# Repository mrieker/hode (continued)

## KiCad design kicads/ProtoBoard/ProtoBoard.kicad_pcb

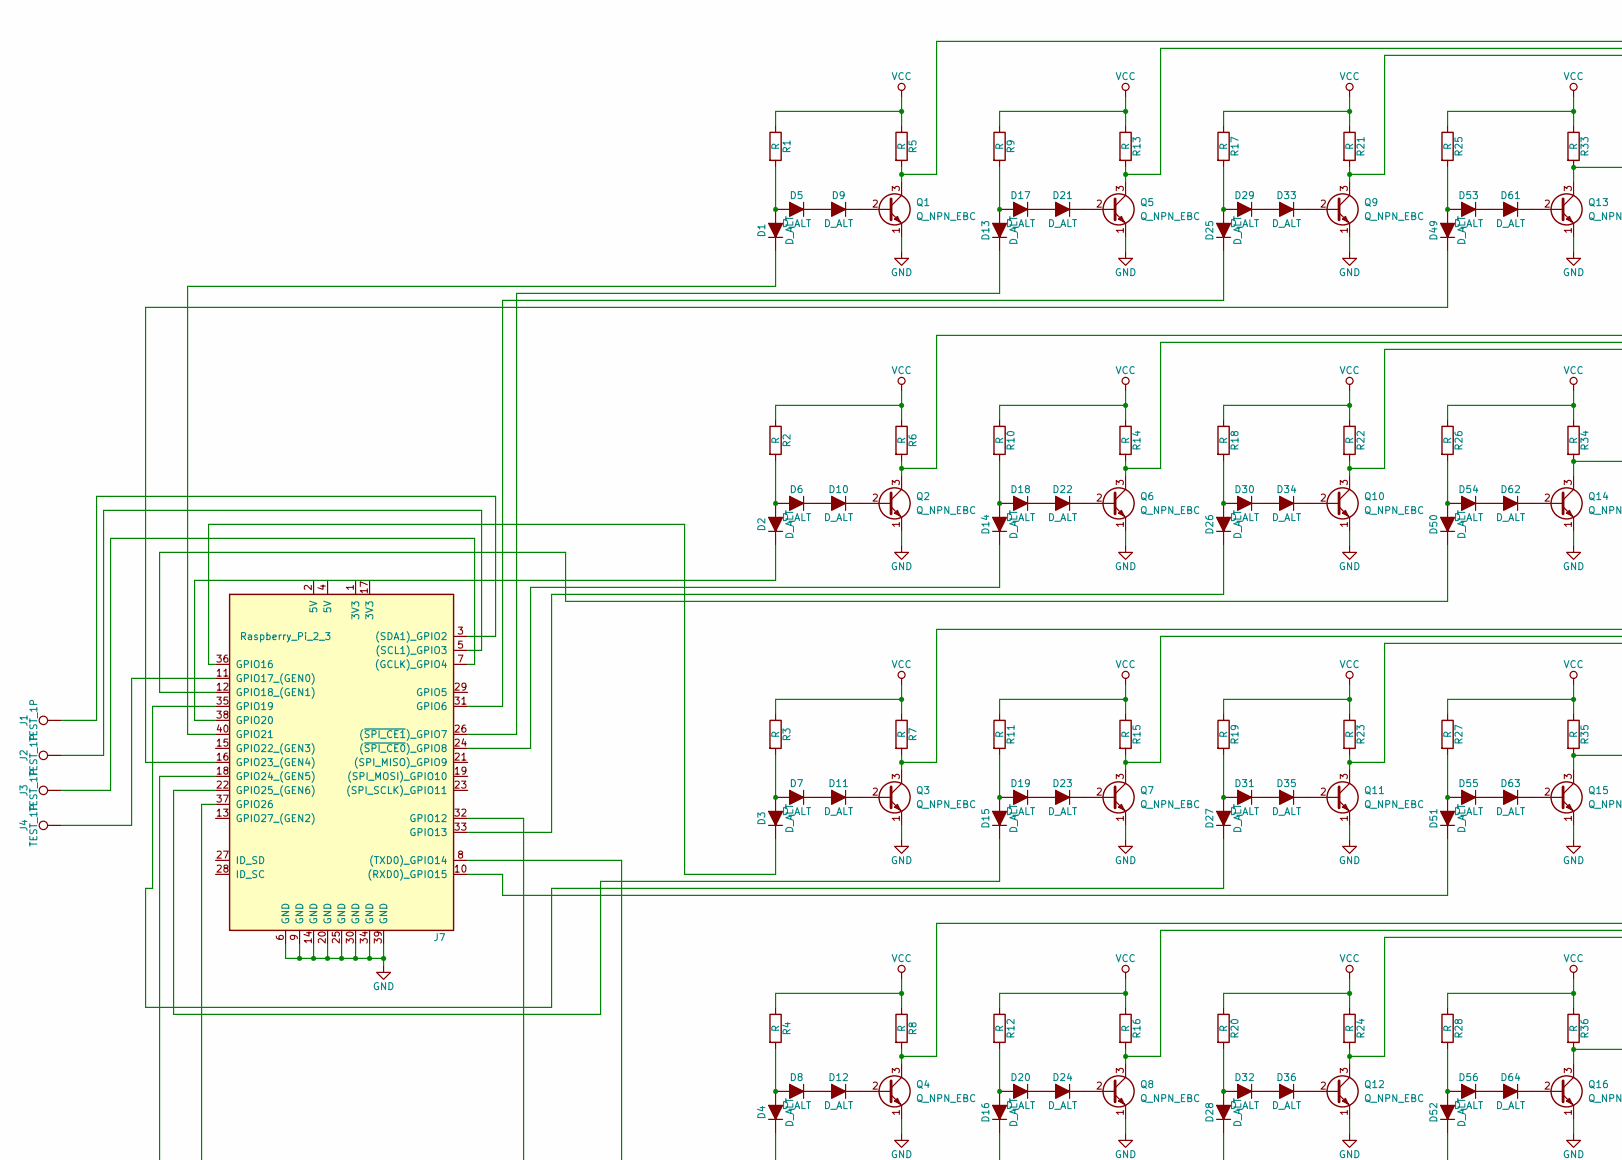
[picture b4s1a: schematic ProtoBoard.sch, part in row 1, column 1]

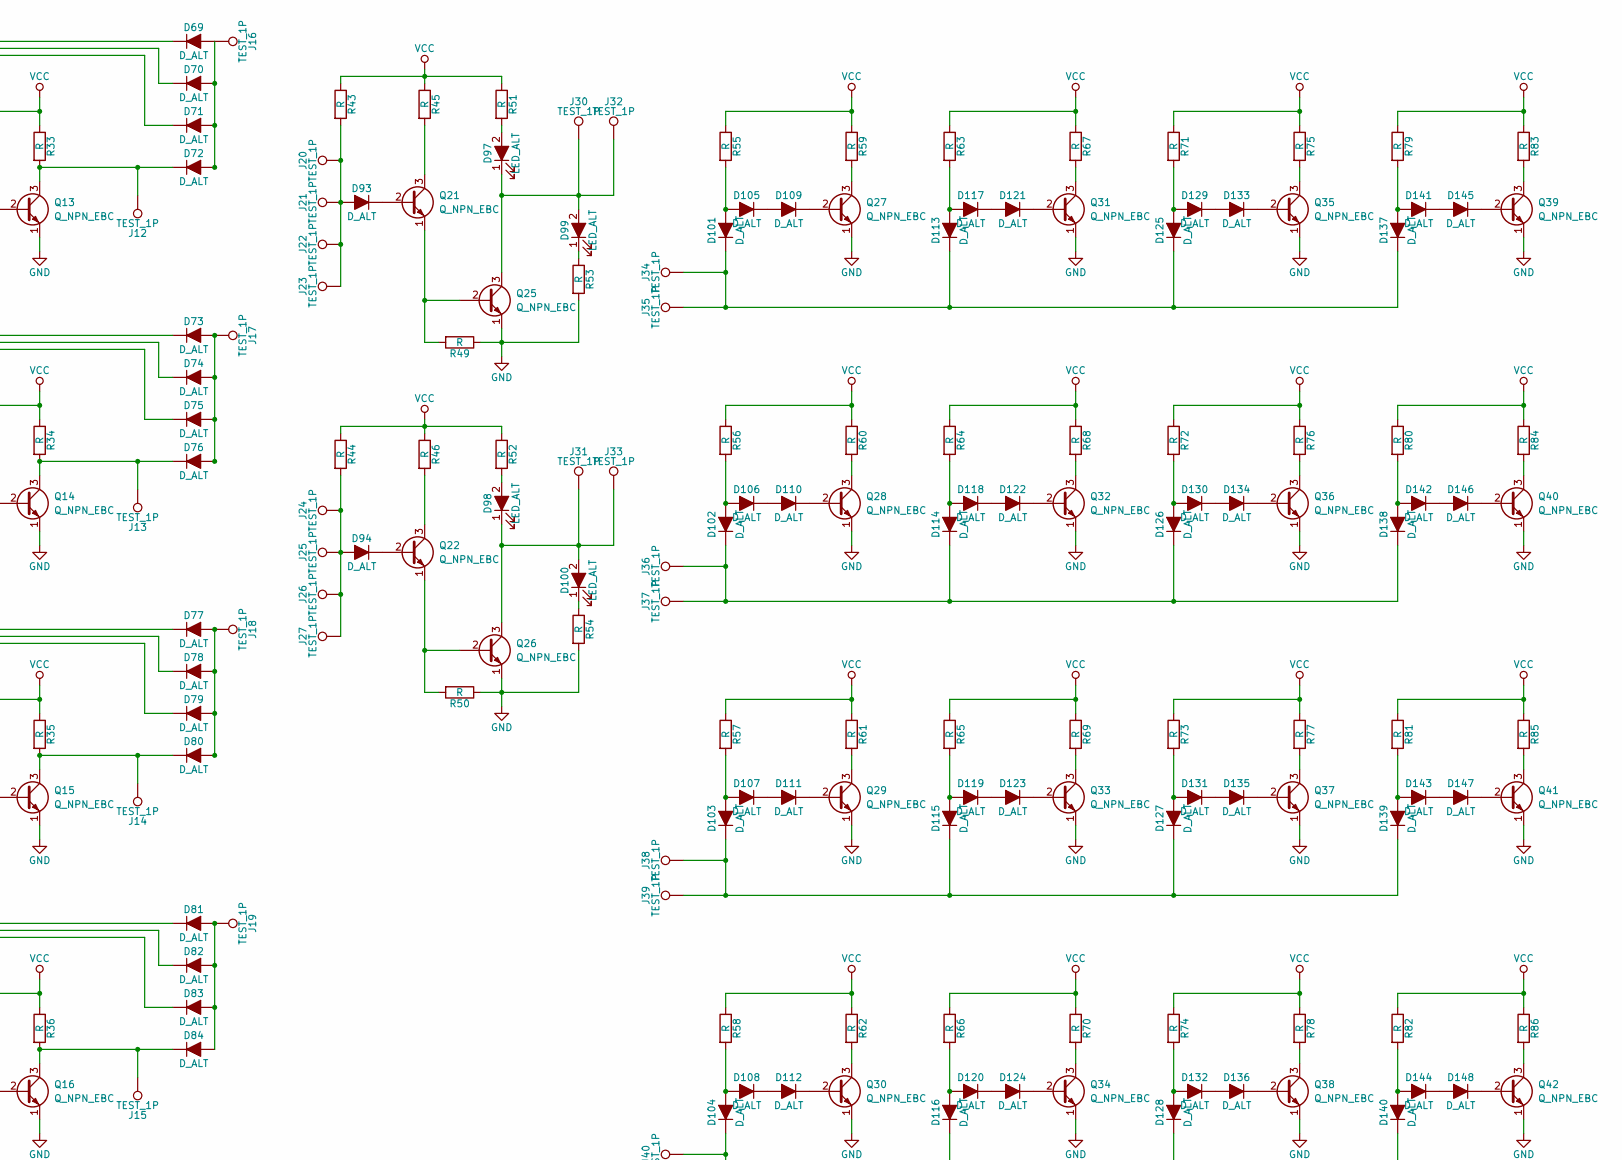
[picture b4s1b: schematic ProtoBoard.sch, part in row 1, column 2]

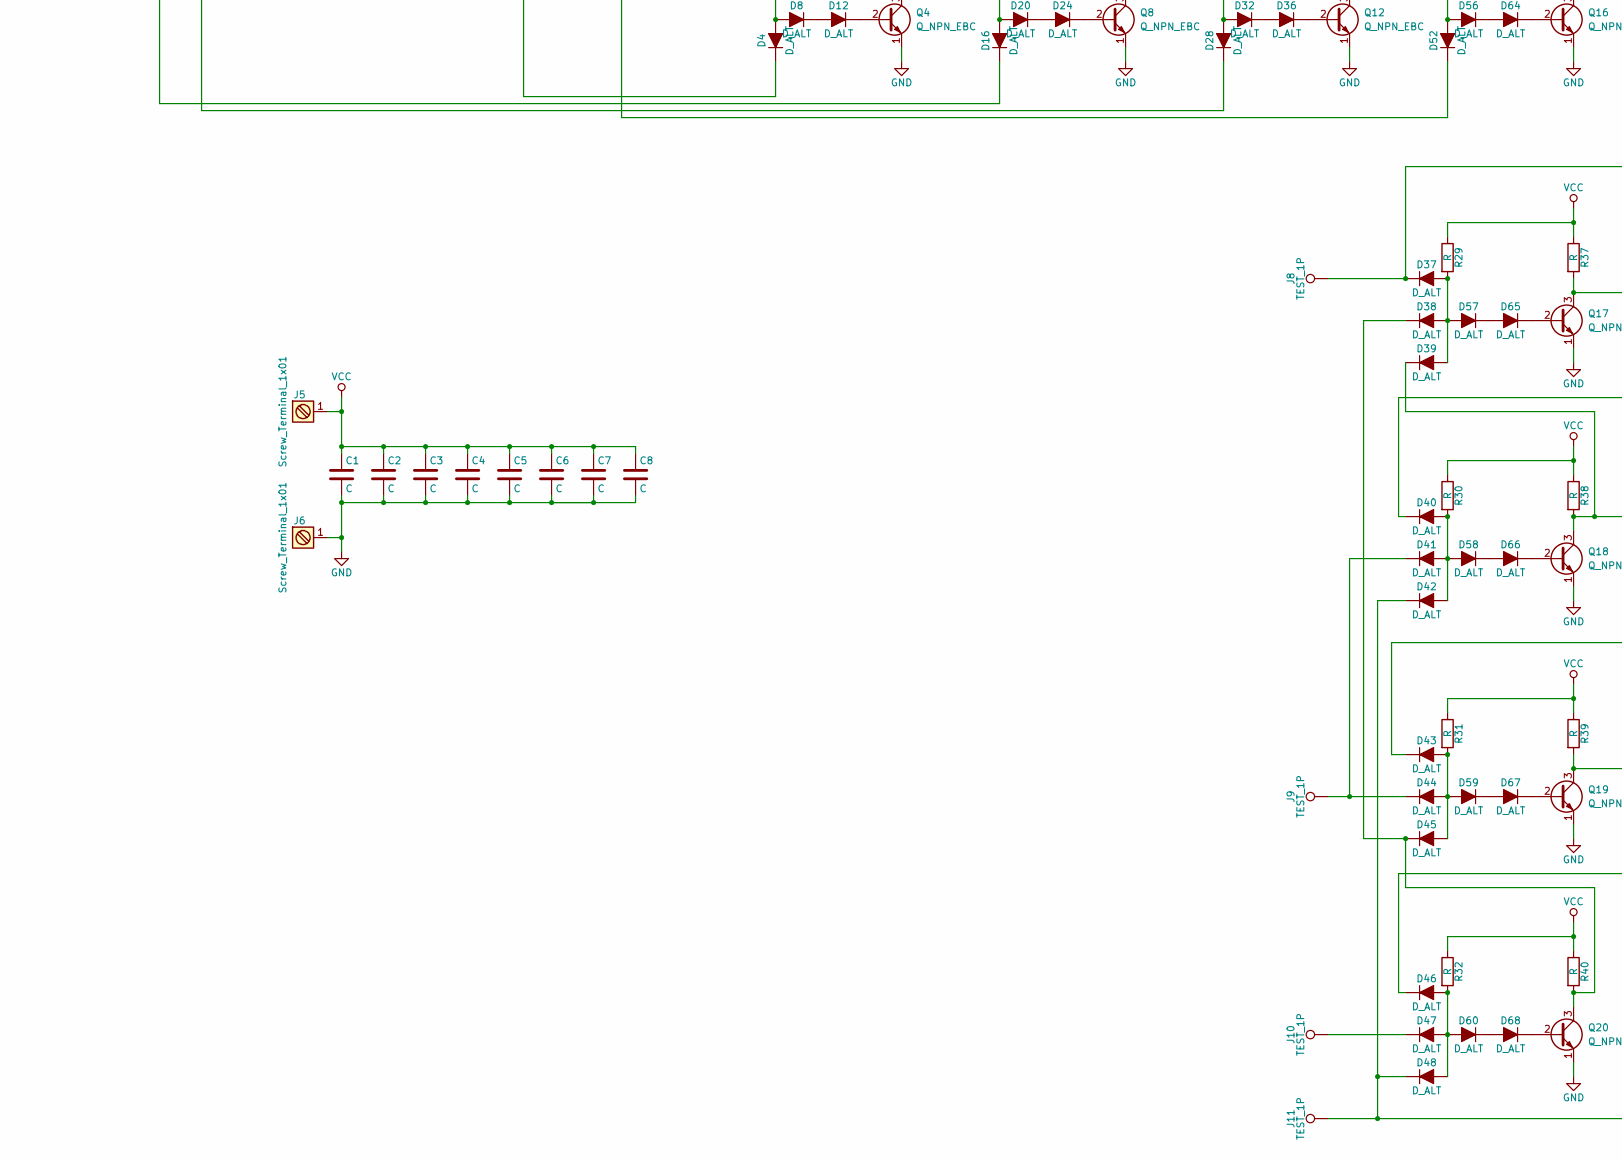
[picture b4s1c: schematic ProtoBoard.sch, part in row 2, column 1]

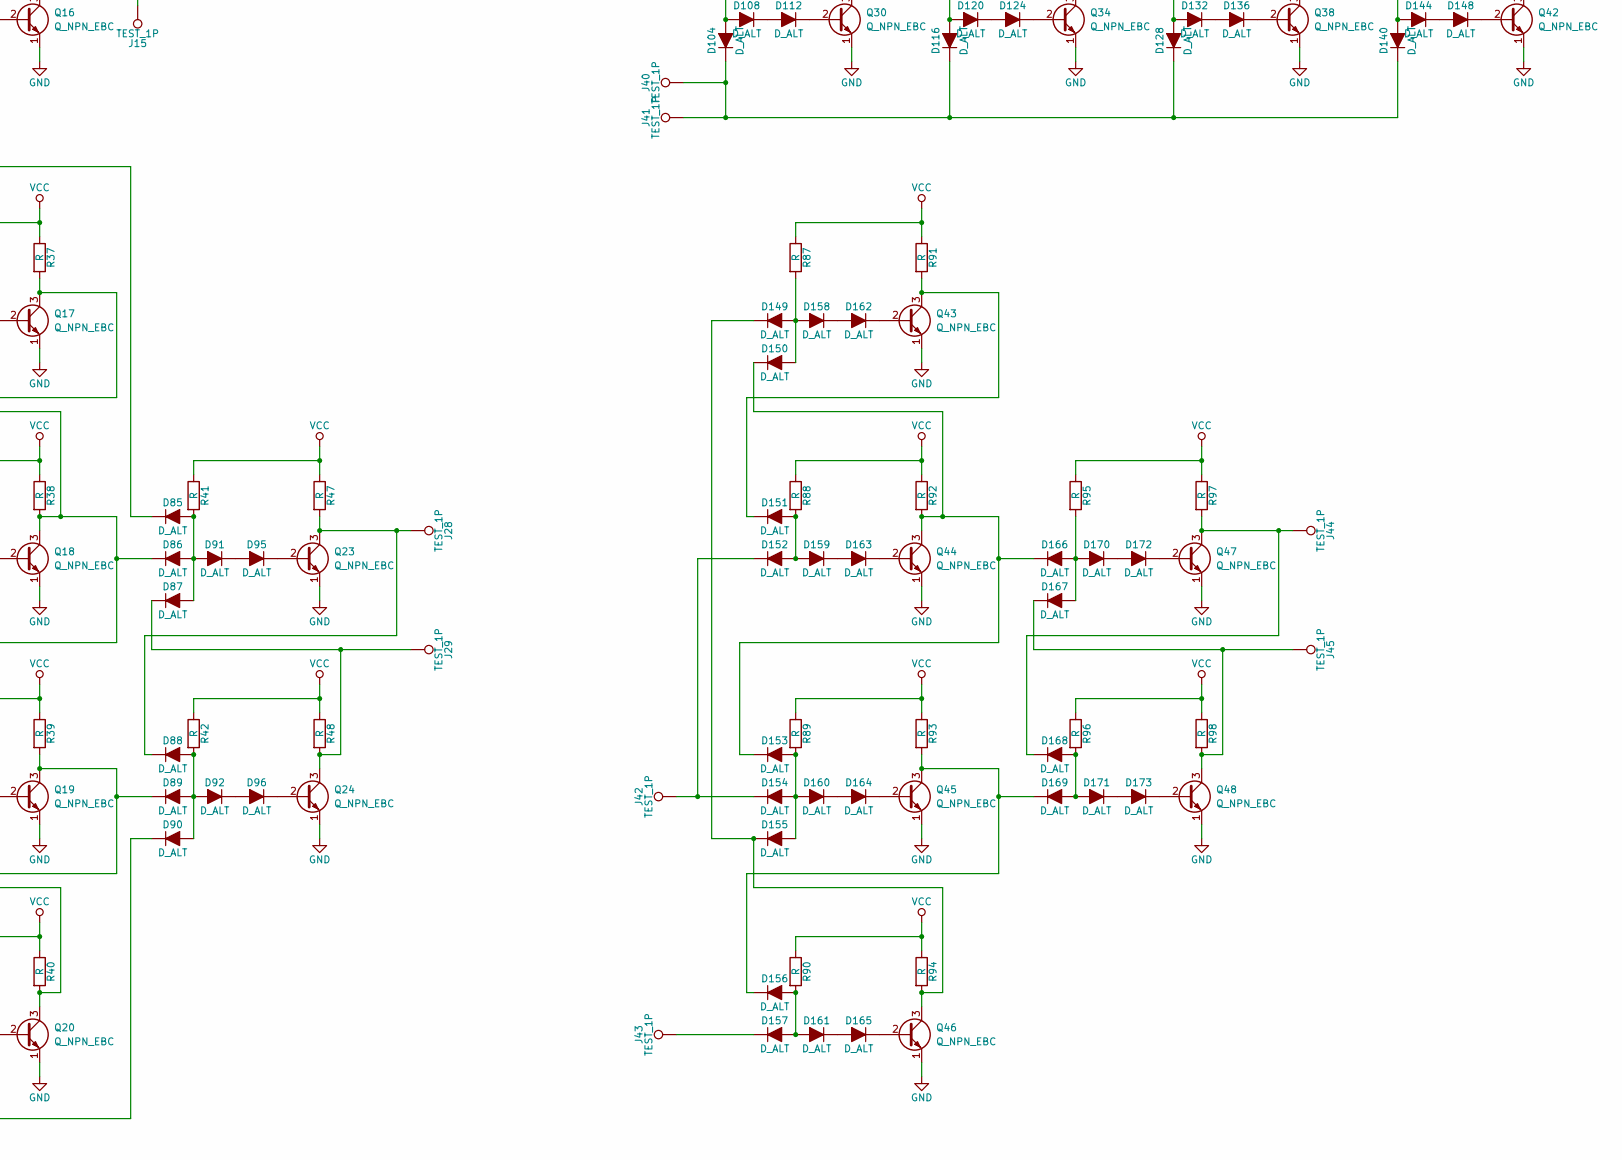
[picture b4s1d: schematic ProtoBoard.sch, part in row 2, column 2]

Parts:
C1, C2, C3, C4, C5, C6, C7, C8: C; C_Axial_L12.0mm_D6.5mm_P15.00mm_Horizontal
D1, D2, D3, D4, D5, D6, D7, D8, D9, D10, D11, D12, D13, D14, D15, D16, D17, D18, D19, D20, D21, D22, D23, D24, D25, D26, D27, D28, D29, D30, D31, D32, D33, D34, D35, D36, D37, D38, D39, D40, D41, D42, D43, D44, D45, D46, D47, D48, D49, D50, D51, D52, D53, D54, D55, D56, D57, D58, D59, D60, D61, D62, D63, D64, D65, D66, D67, D68, D69, D70, D71, D72, D73, D74, D75, D76, D77, D78, D79, D80, D81, D82, D83, D84, D85, D86, D87, D88, D89, D90, D91, D92, D93, D94, D95, D96, D101, D102, D103, D104, D105, D106, D107, D108, D109, D110, D111, D112, D113, D114, D115, D116, D117, D118, D119, D120, D121, D122, D123, D124, D125, D126, D127, D128, D129, D130, D131, D132, D133, D134, D135, D136, D137, D138, D139, D140, D141, D142, D143, D144, D145, D146, D147, D148: D_ALT; D_DO-35_SOD27_P7.62mm_Horizontal
D97, D98, D99, D100: LED_ALT; LED_D3.0mm
D149, D150, D151, D152, D153, D154, D155, D156, D157, D158, D159, D160, D161, D162, D163, D164, D165, D166, D167, D168, D169, D170, D171, D172, D173: D_ALT; D_DO-35_SOD27_P2.54mm_Vertical_KathodeUp
J1, J2, J3, J4, J8, J9, J10, J11, J12, J13, J14, J15, J16, J17, J18, J19, J20, J21, J22, J23, J24, J25, J26, J27, J28, J29, J30, J31, J32, J33, J34, J35, J36, J37, J38, J39, J40, J41, J42, J43, J44, J45: TEST_1P; 1pin
J5, J6: Screw_Terminal_1x01; 1pin
J7: Raspberry_Pi_2_3; Multicomp_MC9A12-4034_2x20x2.54mm_Straight
Q1, Q2, Q3, Q4, Q5, Q6, Q7, Q8, Q9, Q10, Q11, Q12, Q13, Q14, Q15, Q16, Q17, Q18, Q19, Q20, Q21, Q22, Q23, Q24, Q25, Q26, Q27, Q28, Q29, Q30, Q31, Q32, Q33, Q34, Q35, Q36, Q37, Q38, Q39, Q40, Q41, Q42, Q43, Q44, Q45, Q46, Q47, Q48: Q_NPN_EBC; TO-92_Molded_Wide
R1, R2, R3, R4, R5, R6, R7, R8, R9, R10, R11, R12, R13, R14, R15, R16, R17, R18, R19, R20, R21, R22, R23, R24, R25, R26, R27, R28, R29, R30, R31, R32, R33, R34, R35, R36, R37, R38, R39, R40, R41, R42, R43, R44, R45, R46, R47, R48, R49, R50, R51, R52, R53, R54, R55, R56, R57, R58, R59, R60, R61, R62, R63, R64, R65, R66, R67, R68, R69, R70, R71, R72, R73, R74, R75, R76, R77, R78, R79, R80, R81, R82, R83, R84, R85, R86: R; R_Axial_DIN0207_L6.3mm_D2.5mm_P10.16mm_Horizontal
R87, R88, R89, R90, R91, R92, R93, R94, R95, R96, R97, R98: R; R_Axial_DIN0207_L6.3mm_D2.5mm_P2.54mm_Vertical

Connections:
GND: C1.2, C2.2, C3.2, C4.2, C5.2, C6.2, C7.2, C8.2, J6.1, J7.6 (GND), J7.9 (GND), J7.14 (GND), J7.20 (GND), J7.25 (GND), J7.30 (GND), J7.34 (GND), J7.39 (GND), Q1.1 (E), Q2.1 (E), Q3.1 (E), Q4.1 (E), Q5.1 (E), Q6.1 (E), Q7.1 (E), Q8.1 (E), Q9.1 (E), Q10.1 (E), Q11.1 (E), Q12.1 (E), Q13.1 (E), Q14.1 (E), Q15.1 (E), Q16.1 (E), Q17.1 (E), Q18.1 (E), Q19.1 (E), Q20.1 (E), Q23.1 (E), Q24.1 (E), Q25.1 (E), Q26.1 (E), Q27.1 (E), Q28.1 (E), Q29.1 (E), Q30.1 (E), Q31.1 (E), Q32.1 (E), Q33.1 (E), Q34.1 (E), Q35.1 (E), Q36.1 (E), Q37.1 (E), Q38.1 (E), Q39.1 (E), Q40.1 (E), Q41.1 (E), Q42.1 (E), Q43.1 (E), Q44.1 (E), Q45.1 (E), Q46.1 (E), Q47.1 (E), Q48.1 (E), R49.1, R50.1, R53.2, R54.2
unnamed: D1.1 (K), J7.40 (GPIO21)
unnamed: D1.2 (A), D5.2 (A), R1.2
unnamed: D2.1 (K), J7.38 (GPIO20)
unnamed: D2.2 (A), D6.2 (A), R2.2
unnamed: D3.1 (K), J7.36 (GPIO16)
unnamed: D3.2 (A), D7.2 (A), R3.2
unnamed: D4.1 (K), J7.32 (GPIO12)
unnamed: D4.2 (A), D8.2 (A), R4.2
unnamed: D5.1 (K), D9.2 (A)
unnamed: D9.1 (K), Q1.2 (B)
unnamed: D10.1 (K), Q2.2 (B)
unnamed: D6.1 (K), D10.2 (A)
unnamed: D11.1 (K), Q3.2 (B)
unnamed: D7.1 (K), D11.2 (A)
unnamed: D12.1 (K), Q4.2 (B)
unnamed: D8.1 (K), D12.2 (A)
unnamed: D13.1 (K), J7.26 ((~SPI_CE1~)_GPIO7)
unnamed: D13.2 (A), D17.2 (A), R9.2
unnamed: D14.1 (K), J7.24 ((~SPI_CE0~)_GPIO8)
unnamed: D14.2 (A), D18.2 (A), R10.2
unnamed: D15.1 (K), J7.22 (GPIO25_(GEN6))
unnamed: D15.2 (A), D19.2 (A), R11.2
unnamed: D16.1 (K), J7.18 (GPIO24_(GEN5))
unnamed: D16.2 (A), D20.2 (A), R12.2
unnamed: D17.1 (K), D21.2 (A)
unnamed: D18.1 (K), D22.2 (A)
unnamed: D19.1 (K), D23.2 (A)
unnamed: D20.1 (K), D24.2 (A)
unnamed: D21.1 (K), Q5.2 (B)
unnamed: D22.1 (K), Q6.2 (B)
unnamed: D23.1 (K), Q7.2 (B)
unnamed: D24.1 (K), Q8.2 (B)
unnamed: D25.1 (K), J7.31 (GPIO6)
unnamed: D25.2 (A), D29.2 (A), R17.2
unnamed: D26.1 (K), J7.33 (GPIO13)
unnamed: D26.2 (A), D30.2 (A), R18.2
unnamed: D27.1 (K), J7.35 (GPIO19)
unnamed: D27.2 (A), D31.2 (A), R19.2
unnamed: D28.1 (K), J7.37 (GPIO26)
unnamed: D28.2 (A), D32.2 (A), R20.2
unnamed: D29.1 (K), D33.2 (A)
unnamed: D30.1 (K), D34.2 (A)
unnamed: D31.1 (K), D35.2 (A)
unnamed: D32.1 (K), D36.2 (A)
unnamed: D33.1 (K), Q9.2 (B)
unnamed: D34.1 (K), Q10.2 (B)
unnamed: D35.1 (K), Q11.2 (B)
unnamed: D36.1 (K), Q12.2 (B)
unnamed: D37.1 (K), D85.1 (K), J8.1
unnamed: D37.2 (A), D38.2 (A), D39.2 (A), D57.2 (A), R29.2
unnamed: D38.1 (K), D45.1 (K), Q20.3 (C), R40.2
unnamed: D39.1 (K), D43.1 (K), D86.1 (K), Q18.3 (C), R38.2
unnamed: D40.1 (K), Q17.3 (C), R37.2
unnamed: D40.2 (A), D41.2 (A), D42.2 (A), D58.2 (A), R30.2
unnamed: D41.1 (K), D44.1 (K), J9.1
unnamed: D42.1 (K), D48.1 (K), D90.1 (K), J11.1
unnamed: D43.2 (A), D44.2 (A), D45.2 (A), D59.2 (A), R31.2
unnamed: D46.1 (K), D89.1 (K), Q19.3 (C), R39.2
unnamed: D46.2 (A), D47.2 (A), D48.2 (A), D60.2 (A), R32.2
unnamed: D47.1 (K), J10.1
unnamed: D49.1 (K), J7.16 (GPIO23_(GEN4))
unnamed: D49.2 (A), D53.2 (A), R25.2
unnamed: D50.1 (K), J7.12 (GPIO18_(GEN1))
unnamed: D50.2 (A), D54.2 (A), R26.2
unnamed: D51.1 (K), J7.10 ((RXD0)_GPIO15)
unnamed: D51.2 (A), D55.2 (A), R27.2
unnamed: D52.1 (K), J7.8 ((TXD0)_GPIO14)
unnamed: D52.2 (A), D56.2 (A), R28.2
unnamed: D53.1 (K), D61.2 (A)
unnamed: D54.1 (K), D62.2 (A)
unnamed: D55.1 (K), D63.2 (A)
unnamed: D56.1 (K), D64.2 (A)
unnamed: D57.1 (K), D65.2 (A)
unnamed: D58.1 (K), D66.2 (A)
unnamed: D59.1 (K), D67.2 (A)
unnamed: D60.1 (K), D68.2 (A)
unnamed: D61.1 (K), Q13.2 (B)
unnamed: D62.1 (K), Q14.2 (B)
unnamed: D63.1 (K), Q15.2 (B)
unnamed: D64.1 (K), Q16.2 (B)
unnamed: D65.1 (K), Q17.2 (B)
unnamed: D66.1 (K), Q18.2 (B)
unnamed: D67.1 (K), Q19.2 (B)
unnamed: D68.1 (K), Q20.2 (B)
unnamed: D69.1 (K), Q1.3 (C), R5.2
unnamed: D69.2 (A), D70.2 (A), D71.2 (A), D72.2 (A), J16.1
unnamed: D70.1 (K), Q5.3 (C), R13.2
unnamed: D71.1 (K), Q9.3 (C), R21.2
unnamed: D72.1 (K), J12.1, Q13.3 (C), R33.2
unnamed: D73.1 (K), Q2.3 (C), R6.2
unnamed: D73.2 (A), D74.2 (A), D75.2 (A), D76.2 (A), J17.1
unnamed: D74.1 (K), Q6.3 (C), R14.2
unnamed: D75.1 (K), Q10.3 (C), R22.2
unnamed: D76.1 (K), J13.1, Q14.3 (C), R34.2
unnamed: D77.1 (K), Q3.3 (C), R7.2
unnamed: D77.2 (A), D78.2 (A), D79.2 (A), D80.2 (A), J18.1
unnamed: D78.1 (K), Q7.3 (C), R15.2
unnamed: D79.1 (K), Q11.3 (C), R23.2
unnamed: D80.1 (K), J14.1, Q15.3 (C), R35.2
unnamed: D81.1 (K), Q4.3 (C), R8.2
unnamed: D81.2 (A), D82.2 (A), D83.2 (A), D84.2 (A), J19.1
unnamed: D82.1 (K), Q8.3 (C), R16.2
unnamed: D83.1 (K), Q12.3 (C), R24.2
unnamed: D84.1 (K), J15.1, Q16.3 (C), R36.2
unnamed: D85.2 (A), D86.2 (A), D87.2 (A), D91.2 (A), R41.2
unnamed: D87.1 (K), J29.1, Q24.3 (C), R48.2
unnamed: D88.1 (K), J28.1, Q23.3 (C), R47.2
unnamed: D88.2 (A), D89.2 (A), D90.2 (A), D92.2 (A), R42.2
unnamed: D91.1 (K), D95.2 (A)
unnamed: D92.1 (K), D96.2 (A)
unnamed: D93.1 (K), Q21.2 (B)
unnamed: D93.2 (A), J20.1, J21.1, J22.1, J23.1, R43.2
unnamed: D94.1 (K), Q22.2 (B)
unnamed: D94.2 (A), J24.1, J25.1, J26.1, J27.1, R44.2
unnamed: D95.1 (K), Q23.2 (B)
unnamed: D96.1 (K), Q24.2 (B)
unnamed: D97.1 (K), D99.2 (A), J30.1, J32.1, Q25.3 (C)
unnamed: D97.2 (A), R51.2
unnamed: D98.2 (A), R52.2
unnamed: D99.1 (K), R53.1
unnamed: D100.1 (K), R54.1
unnamed: D98.1 (K), D100.2 (A), J31.1, J33.1, Q26.3 (C)
unnamed: D101.1 (K), D113.1 (K), D125.1 (K), D137.1 (K), J34.1, J35.1
unnamed: D101.2 (A), D105.2 (A), R55.2
unnamed: D102.1 (K), D114.1 (K), D126.1 (K), D138.1 (K), J36.1, J37.1
unnamed: D102.2 (A), D106.2 (A), R56.2
unnamed: D103.1 (K), D115.1 (K), D127.1 (K), D139.1 (K), J38.1, J39.1
unnamed: D103.2 (A), D107.2 (A), R57.2
unnamed: D104.1 (K), D116.1 (K), D128.1 (K), D140.1 (K), J40.1, J41.1
unnamed: D104.2 (A), D108.2 (A), R58.2
unnamed: D105.1 (K), D109.2 (A)
unnamed: D106.1 (K), D110.2 (A)
unnamed: D107.1 (K), D111.2 (A)
unnamed: D108.1 (K), D112.2 (A)
unnamed: D109.1 (K), Q27.2 (B)
unnamed: D110.1 (K), Q28.2 (B)
unnamed: D111.1 (K), Q29.2 (B)
unnamed: D112.1 (K), Q30.2 (B)
unnamed: D113.2 (A), D117.2 (A), R63.2
unnamed: D114.2 (A), D118.2 (A), R64.2
unnamed: D115.2 (A), D119.2 (A), R65.2
unnamed: D116.2 (A), D120.2 (A), R66.2
unnamed: D117.1 (K), D121.2 (A)
unnamed: D118.1 (K), D122.2 (A)
unnamed: D119.1 (K), D123.2 (A)
unnamed: D120.1 (K), D124.2 (A)
unnamed: D121.1 (K), Q31.2 (B)
unnamed: D122.1 (K), Q32.2 (B)
unnamed: D123.1 (K), Q33.2 (B)
unnamed: D124.1 (K), Q34.2 (B)
unnamed: D125.2 (A), D129.2 (A), R71.2
unnamed: D126.2 (A), D130.2 (A), R72.2
unnamed: D127.2 (A), D131.2 (A), R73.2
unnamed: D128.2 (A), D132.2 (A), R74.2
unnamed: D129.1 (K), D133.2 (A)
unnamed: D130.1 (K), D134.2 (A)
unnamed: D131.1 (K), D135.2 (A)
unnamed: D132.1 (K), D136.2 (A)
unnamed: D133.1 (K), Q35.2 (B)
unnamed: D134.1 (K), Q36.2 (B)
unnamed: D135.1 (K), Q37.2 (B)
unnamed: D136.1 (K), Q38.2 (B)
unnamed: D137.2 (A), D141.2 (A), R79.2
unnamed: D138.2 (A), D142.2 (A), R80.2
unnamed: D139.2 (A), D143.2 (A), R81.2
unnamed: D140.2 (A), D144.2 (A), R82.2
unnamed: D141.1 (K), D145.2 (A)
unnamed: D142.1 (K), D146.2 (A)
unnamed: D143.1 (K), D147.2 (A)
unnamed: D144.1 (K), D148.2 (A)
unnamed: D145.1 (K), Q39.2 (B)
unnamed: D146.1 (K), Q40.2 (B)
unnamed: D147.1 (K), Q41.2 (B)
unnamed: D148.1 (K), Q42.2 (B)
unnamed: D149.1 (K), D155.1 (K), Q46.3 (C), R94.2
unnamed: D149.2 (A), D150.2 (A), D158.2 (A), R87.2
unnamed: D150.1 (K), D153.1 (K), D166.1 (K), Q44.3 (C), R92.2
unnamed: D151.1 (K), Q43.3 (C), R91.2
unnamed: D151.2 (A), D152.2 (A), D159.2 (A), R88.2
unnamed: D152.1 (K), D154.1 (K), J42.1
unnamed: D153.2 (A), D154.2 (A), D155.2 (A), D160.2 (A), R89.2
unnamed: D156.1 (K), D169.1 (K), Q45.3 (C), R93.2
unnamed: D156.2 (A), D157.2 (A), D161.2 (A), R90.2
unnamed: D157.1 (K), J43.1
unnamed: D158.1 (K), D162.2 (A)
unnamed: D159.1 (K), D163.2 (A)
unnamed: D160.1 (K), D164.2 (A)
unnamed: D161.1 (K), D165.2 (A)
unnamed: D162.1 (K), Q43.2 (B)
unnamed: D163.1 (K), Q44.2 (B)
unnamed: D164.1 (K), Q45.2 (B)
unnamed: D165.1 (K), Q46.2 (B)
unnamed: D166.2 (A), D167.2 (A), D170.2 (A), R95.2
unnamed: D167.1 (K), J45.1, Q48.3 (C), R98.2
unnamed: D168.1 (K), J44.1, Q47.3 (C), R97.2
unnamed: D168.2 (A), D169.2 (A), D171.2 (A), R96.2
unnamed: D170.1 (K), D172.2 (A)
unnamed: D171.1 (K), D173.2 (A)
unnamed: D172.1 (K), Q47.2 (B)
unnamed: D173.1 (K), Q48.2 (B)
unnamed: J1.1, J7.3 ((SDA1)_GPIO2)
unnamed: J2.1, J7.5 ((SCL1)_GPIO3)
unnamed: J3.1, J7.7 ((GCLK)_GPIO4)
unnamed: J4.1, J7.11 (GPIO17_(GEN0))
unnamed: Q21.1 (E), Q25.2 (B), R49.2
unnamed: Q21.3 (C), R45.2
unnamed: Q22.1 (E), Q26.2 (B), R50.2
unnamed: Q22.3 (C), R46.2
unnamed: Q27.3 (C), R59.2
unnamed: Q28.3 (C), R60.2
unnamed: Q29.3 (C), R61.2
unnamed: Q30.3 (C), R62.2
unnamed: Q31.3 (C), R67.2
unnamed: Q32.3 (C), R68.2
unnamed: Q33.3 (C), R69.2
unnamed: Q34.3 (C), R70.2
unnamed: Q35.3 (C), R75.2
unnamed: Q36.3 (C), R76.2
unnamed: Q37.3 (C), R77.2
unnamed: Q38.3 (C), R78.2
unnamed: Q39.3 (C), R83.2
unnamed: Q40.3 (C), R84.2
unnamed: Q41.3 (C), R85.2
unnamed: Q42.3 (C), R86.2
VCC: C1.1, C2.1, C3.1, C4.1, C5.1, C6.1, C7.1, C8.1, J5.1, R1.1, R2.1, R3.1, R4.1, R5.1, R6.1, R7.1, R8.1, R9.1, R10.1, R11.1, R12.1, R13.1, R14.1, R15.1, R16.1, R17.1, R18.1, R19.1, R20.1, R21.1, R22.1, R23.1, R24.1, R25.1, R26.1, R27.1, R28.1, R29.1, R30.1, R31.1, R32.1, R33.1, R34.1, R35.1, R36.1, R37.1, R38.1, R39.1, R40.1, R41.1, R42.1, R43.1, R44.1, R45.1, R46.1, R47.1, R48.1, R51.1, R52.1, R55.1, R56.1, R57.1, R58.1, R59.1, R60.1, R61.1, R62.1, R63.1, R64.1, R65.1, R66.1, R67.1, R68.1, R69.1, R70.1, R71.1, R72.1, R73.1, R74.1, R75.1, R76.1, R77.1, R78.1, R79.1, R80.1, R81.1, R82.1, R83.1, R84.1, R85.1, R86.1, R87.1, R88.1, R89.1, R90.1, R91.1, R92.1, R93.1, R94.1, R95.1, R96.1, R97.1, R98.1

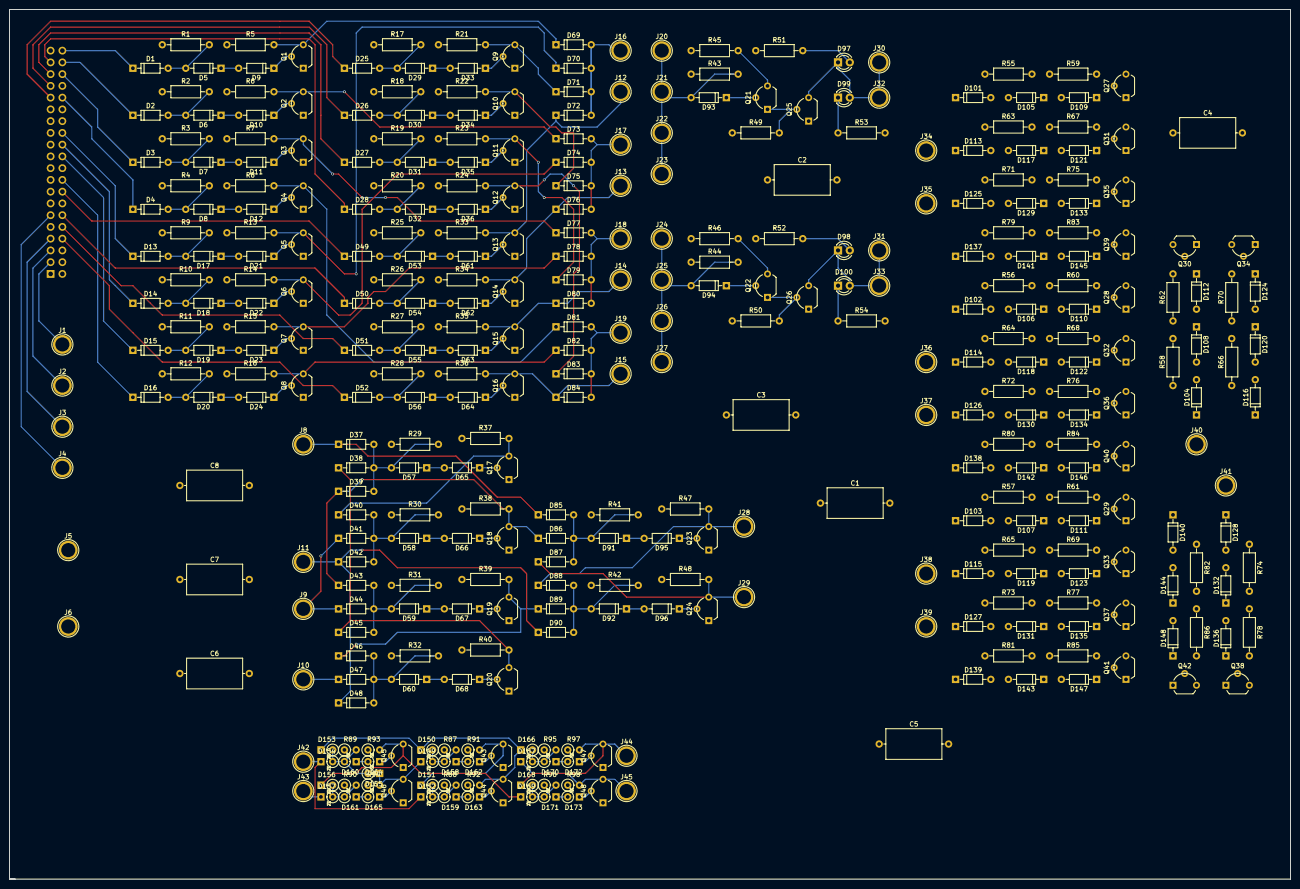
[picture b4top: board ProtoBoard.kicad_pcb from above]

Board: 4 copper layers, 276.9 x 188.0 mm, 372 parts (1 on the bottom side), 226 nets.

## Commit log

2022-03-06 initial release
2022-03-15 bunch of new runtime library stuff plus some small compiler fixes
    assembler not barf on long compiler source lines
    define symbol __HODE__ in preprocessor
    handle compiling 1.0/0.0 as a NAN
    make sure testprim gets value in range
    check for finally duplicate label prim optimized out
    optimize anding a larger int size with a smaller int size to give smaller int size
2022-03-25 some compiler and runtime fixes
    compiler fixes
    - fix outputting multiple vtable copies
    - compile script work from any directory and allow multiple source files
    - "and" of two ints result is size of smaller int
    - arith on two small int constants needing bigger result size
    - fix some null pointer crashes after reporting errors
2022-04-02 various updates
    fix not linking unreferenced library modules
    fix compiling ? : numerics of different sizes
    write calculator input/output to log file calc.log
    add degree/radian selection in calculator
    change one-liner stdio functions to macros
    complex trancendental functions with imag=0 use real-only funcs where possible
2022-04-10 cc compiler fixes
    cc compiler:
    fix delete vs delete[]
    fix type:: in calling obj->type::meth()
    calculator:
    add user defined functions
    add help command
2022-05-29 add de0 implementation and some small fixes
    add de0-nano fpga implementation
    calc program:
    * fix mem leak
    * add @ operator to enter complex numbers as magnitude @ angle
    c runtime:
    * add getnowns(), gmtime(), gmtime_r(), time(), timegm()
2022-06-16 three small fixes
    load, save commands for crtl/calc demo program
    fix driver/raspictl script running from other directories
    update readme with de0 nano info and other little fixes
